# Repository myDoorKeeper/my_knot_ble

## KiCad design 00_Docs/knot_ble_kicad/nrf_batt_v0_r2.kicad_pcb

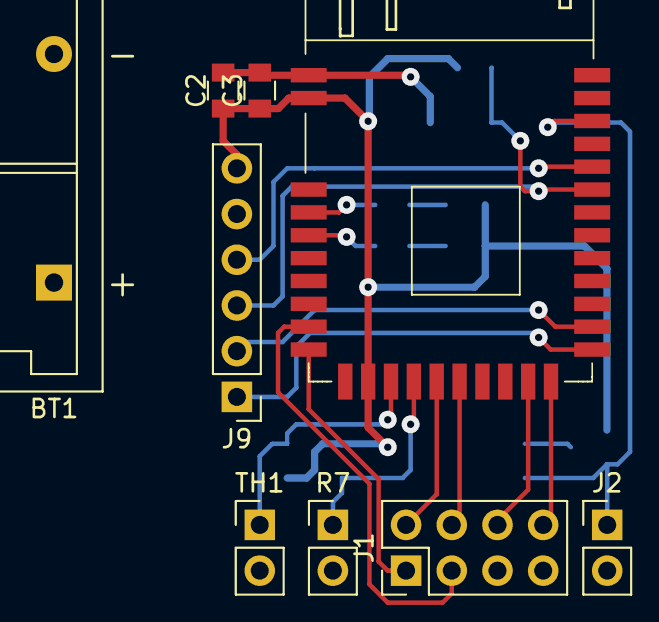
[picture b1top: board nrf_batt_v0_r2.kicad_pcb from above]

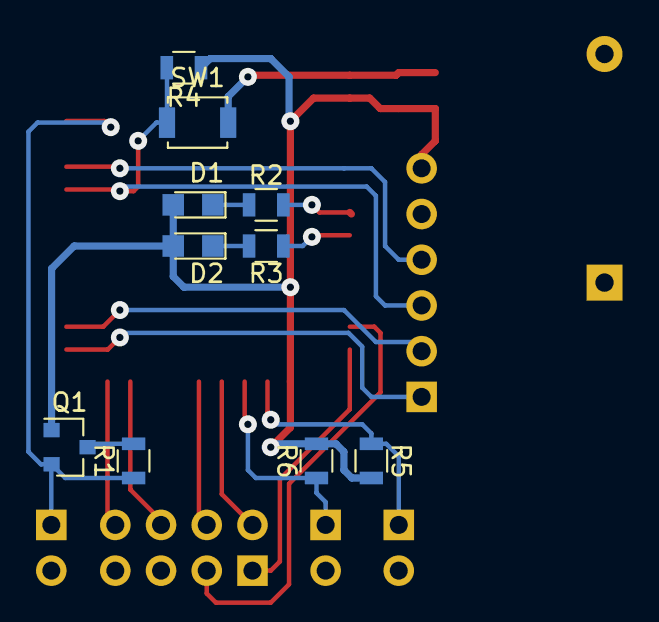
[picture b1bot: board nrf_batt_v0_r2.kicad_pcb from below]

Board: 2 copper layers, 19 parts (10 on the bottom side), 18 nets.

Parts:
BT1: Battery; Keystone_2468_2xAAA
C2: 1uF; C_0805
C3: 100nF; C_0805
D1, D2: LED; LED_0805
J1: Conn_01x08; Pin_Header_Straight_2x04_Pitch2.54mm
J2: Door_Sensor; Pin_Header_Straight_1x02_Pitch2.54mm
J9: Conn_DAP; Pin_Header_Straight_1x06_Pitch2.54mm
Q1: Q_PMOS_DGS; SOT-23
R1, R5: 10K; R_0805
R2, R3, R4: 1K; R_0805
R6: 100K; R_0805
R7: LDR03; Pin_Header_Straight_1x02_Pitch2.54mm
SW1: SW_Push; SW_SPST_B3U-1000P
TH1: Thermistor_NTC; Pin_Header_Straight_1x02_Pitch2.54mm
U2: vng_nRF51822_test; MODULE_NRF51822_REV01_1

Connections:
A01: J1.2, U2.15
A02: J1.4, U2.16
BATT_READ: BT1.1, C2.1, C3.1, D1.2, D2.2, J1.7, J9.6, Q1.1, R4.1, R5.2, R6.2, U2.2, U2.12
D01: J1.6, U2.19
D02: J1.8, U2.20
DOOR_READ: J2.1, Q1.2, R1.1, U2.31
GND: BT1.2, C2.2, C3.2, J1.5, J2.2, J9.5, R2.2, R3.2, R7.2, SW1.2, TH1.2, U2.1, U2.4, U2.5
I2C_CLK: J1.1, U2.10
I2C_DATA: J1.3, U2.9
LDR_READ: R6.1, R7.1, U2.14
NTC_READ: R5.1, TH1.1, U2.13
unnamed: D1.1, R2.1
unnamed: D2.1, R3.1
unnamed: Q1.3, R1.2
RX_DAP: J9.2, U2.22
SWCLK_DAP: J9.4, U2.29
SWDIO_DAP: J9.3, R4.2, SW1.1, U2.28
TX_DAP: J9.1, U2.21

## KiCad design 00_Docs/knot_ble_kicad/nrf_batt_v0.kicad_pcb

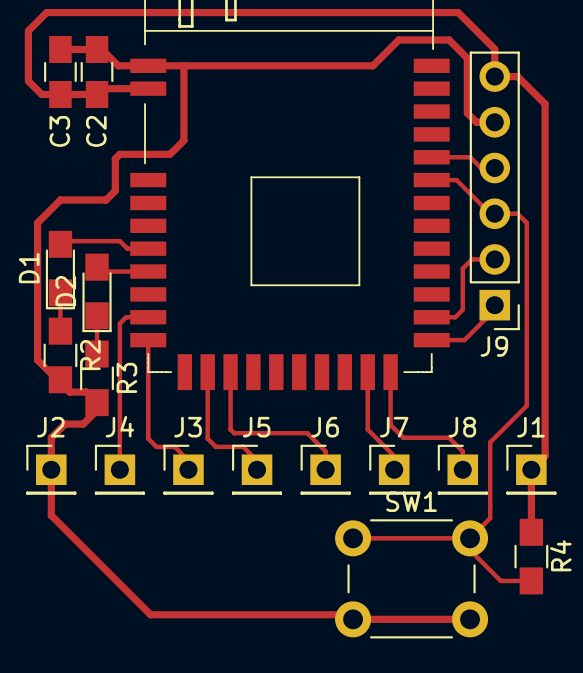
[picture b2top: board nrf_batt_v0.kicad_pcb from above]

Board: 2 copper layers, 18 parts (0 on the bottom side), 16 nets.

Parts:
C2: 1uF; C_0805_HandSoldering
C3: 100nF; C_0805_HandSoldering
D1, D2: LED; LED_0805_HandSoldering
J1: Conn_VCC; Pin_Header_Straight_1x01_Pitch2.54mm
J2: Conn_GND; Pin_Header_Straight_1x01_Pitch2.54mm
J3: Conn_I2C_CLK; Pin_Header_Straight_1x01_Pitch2.54mm
J4: Conn_I2C_DATA; Pin_Header_Straight_1x01_Pitch2.54mm
J5: Conn_A01; Pin_Header_Straight_1x01_Pitch2.54mm
J6: Conn_A02; Pin_Header_Straight_1x01_Pitch2.54mm
J7: Conn_D08; Pin_Header_Straight_1x01_Pitch2.54mm
J8: Conn_D09; Pin_Header_Straight_1x01_Pitch2.54mm
J9: Conn_DAP; Pin_Header_Straight_1x06_Pitch2.54mm
R2, R3, R4: 1K; R_0805_HandSoldering
SW1: SW_Push; SW_PUSH_6mm
U2: vng_nRF51822_test; MODULE_NRF51822_REV01_1

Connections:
A01: J5.1, U2.12
A02: J6.1, U2.13
D08: J7.1, U2.19
D09: J8.1, U2.20
GND: C2.2, C3.2, J2.1, J9.5, R2.2, R3.2, SW1.2, U2.1
I2C_CLK: J3.1, U2.10
I2C_DATA: J4.1, U2.9
LED01: D1.2, U2.6
LED02: D2.2, U2.7
unnamed: D1.1, R2.1
unnamed: D2.1, R3.1
RX_DAP: J9.2, U2.22
SWCLK_DAP: J9.4, U2.29
SWDIO_DAP: J9.3, R4.2, SW1.1, U2.28
TX_DAP: J9.1, U2.21
VCC: C2.1, C3.1, J1.1, J9.6, R4.1, U2.2

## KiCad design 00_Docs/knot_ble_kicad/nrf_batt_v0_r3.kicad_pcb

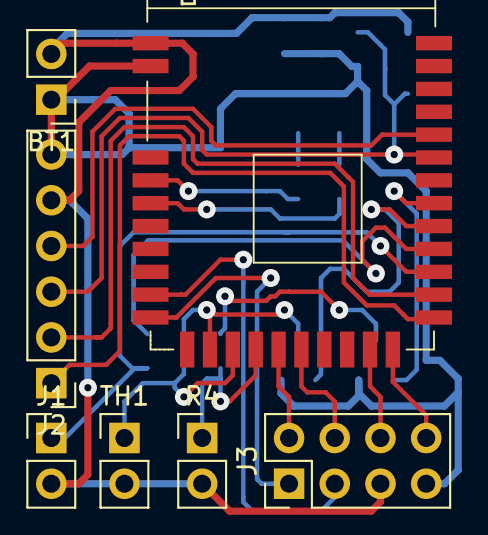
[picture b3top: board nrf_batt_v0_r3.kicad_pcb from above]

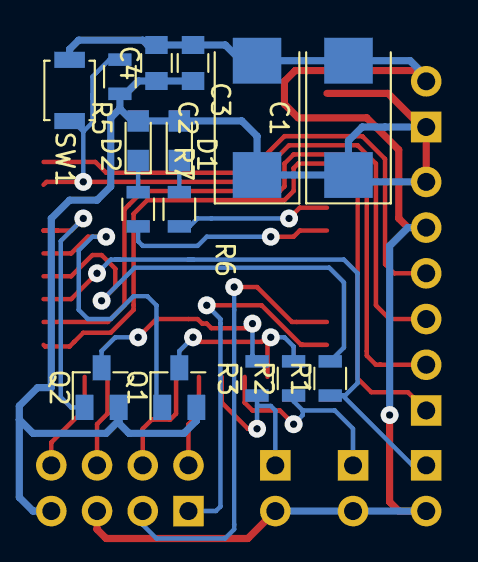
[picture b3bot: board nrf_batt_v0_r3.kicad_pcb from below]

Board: 2 copper layers, 22 parts (15 on the bottom side), 24 nets.

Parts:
BT1: Battery; Pin_Header_Straight_1x02_Pitch2.54mm
C1, C2: 100uF; CP_Tantalum_Case-X_EIA-7343-43_Reflow
C3: 1uF; C_0805
C4: 100nF; C_0805
D1, D2: LED; LED_0805
J1: Door_Sensor; Pin_Header_Straight_1x02_Pitch2.54mm
J2: Conn_DAP; Pin_Header_Straight_1x06_Pitch2.54mm
J3: Conn_01x08; Pin_Header_Straight_2x04_Pitch2.54mm
Q1, Q2: Q_PMOS_GSD; SuperSOT-3
R1, R3: 100K; R_0805
R2: 10K; R_0805
R4: LDR03; Pin_Header_Straight_1x02_Pitch2.54mm
R5, R6, R7: 1K; R_0805
SW1: SW_Push; SW_SPST_B3U-1000P
TH1: Thermistor_NTC; Pin_Header_Straight_1x02_Pitch2.54mm
U1: vng_nRF51822_test; MODULE_NRF51822_REV01_1

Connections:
A01: J3.2, U1.15
A02: J3.4, U1.16
BATT_READ: Q1.3, R2.2, U1.12
BATT_V: BT1.1, C1.1, C2.1, C3.1, C4.1, D1.2, D2.2, J2.6, J3.7, Q1.2, Q2.2, R5.1, U1.2
D01: J3.6, U1.19
D02: J3.8, U1.20
DOOR_CONTROL: R1.2, U1.24
DOOR_READ: J1.1, R1.1, U1.23
GND: BT1.2, C1.2, C2.2, C3.2, C4.2, J1.2, J2.5, J3.5, R4.2, SW1.2, TH1.2, U1.1
I2C_CLK: J3.1, U1.10
I2C_DATA: J3.3, U1.9
LDR_CONTROL: Q2.1, U1.26
LDR_READ: R3.1, R4.1, U1.14
LED01: R6.2, U1.4
LED02: R7.2, U1.5
NTC_CONTROL: Q1.1, U1.25
NTC_READ: R2.1, TH1.1, U1.13
unnamed: D1.1, R6.1
unnamed: D2.1, R7.1
unnamed: Q2.3, R3.2
RX_DAP: J2.2, U1.22
SWCLK_DAP: J2.4, U1.29
SWDIO_DAP: J2.3, R5.2, SW1.1, U1.28
TX_DAP: J2.1, U1.21

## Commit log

2018-02-26 add ble msg doc
2018-02-26 create new revision for knot schematic
2018-03-02 finalize ble_v0_r3
